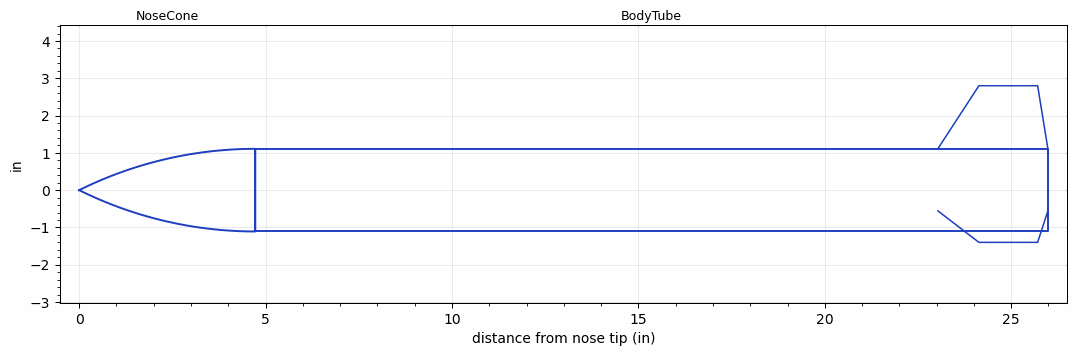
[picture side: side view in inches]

<RASAeroDocument>
 <FileVersion>2</FileVersion>
 <RocketDesign>
  <NoseCone>
   <Length>4.7244</Length>
   <Diameter>2.2165</Diameter>
   <Shape>Tangent Ogive</Shape>
   <Location>0</Location>
  </NoseCone>
  <BodyTube>
   <Length>21.2598</Length>
   <Diameter>2.2165</Diameter>
   <LaunchLugDiameter>0.3937</LaunchLugDiameter>
   <LaunchLugLength>1.1811</LaunchLugLength>
   <Location>4.7244</Location>
   <Fin>
    <Count>3</Count>
    <Chord>2.9527</Chord>
    <Span>1.6929</Span>
    <SweepDistance>1.1024</SweepDistance>
    <TipChord>1.5748</TipChord>
    <Thickness>0.1575</Thickness>
    <Location>2.9527</Location>
    <AirfoilSection>Rounded</AirfoilSection>
   </Fin>
  </BodyTube>
  <Surface>Rough Camouflage Paint</Surface>
  <ModifiedBarrowman>False</ModifiedBarrowman>
  <Turbulence>False</Turbulence>
  <UseBooster1>False</UseBooster1>
  <UseBooster2>False</UseBooster2>
 </RocketDesign>
 <LaunchSite>
  <Altitude>0</Altitude>
  <Pressure>29.9214</Pressure>
  <RodAngle>0</RodAngle>
  <RodLength>78.74</RodLength>
  <Temperature>59</Temperature>
  <WindSpeed>4.4739</WindSpeed>
 </LaunchSite>
 <Recovery>
  <Altitude1>656.168</Altitude1>
  <Altitude2>0</Altitude2>
  <DeviceType1>Parachute</DeviceType1>
  <DeviceType2>None</DeviceType2>
  <Event1>True</Event1>
  <Event2>False</Event2>
  <Size1>11.811</Size1>
  <Size2>0</Size2>
  <EventType1>Apogee</EventType1>
  <EventType2>None</EventType2>
  <CD1>0.8</CD1>
  <CD2>0</CD2>
 </Recovery>
 <SimulationList>
  <Simulation>
   <SustainerEngine>F12J  (AT)</SustainerEngine>
   <SustainerLaunchWt>1.23</SustainerLaunchWt>
   <SustainerCG>13.58</SustainerCG>
   <SustainerIgnitionDelay>0</SustainerIgnitionDelay>
   <Booster1SeparationDelay>0</Booster1SeparationDelay>
   <Booster1IgnitionDelay>0</Booster1IgnitionDelay>
   <IncludeBooster1>False</IncludeBooster1>
   <Booster2Delay>0</Booster2Delay>
   <IncludeBooster2>False</IncludeBooster2>
  </Simulation>
  <Simulation>
   <SustainerEngine>F12J  (AT)</SustainerEngine>
   <SustainerLaunchWt>1.28</SustainerLaunchWt>
   <SustainerCG>14.04</SustainerCG>
   <SustainerIgnitionDelay>0</SustainerIgnitionDelay>
   <Booster1SeparationDelay>0</Booster1SeparationDelay>
   <Booster1IgnitionDelay>0</Booster1IgnitionDelay>
   <IncludeBooster1>False</IncludeBooster1>
   <Booster2Delay>0</Booster2Delay>
   <IncludeBooster2>False</IncludeBooster2>
  </Simulation>
  <Simulation>
   <SustainerLaunchWt>1.2697</SustainerLaunchWt>
   <SustainerCG>13.8432</SustainerCG>
   <SustainerIgnitionDelay>0</SustainerIgnitionDelay>
   <Booster1SeparationDelay>0</Booster1SeparationDelay>
   <Booster1IgnitionDelay>0</Booster1IgnitionDelay>
   <IncludeBooster1>False</IncludeBooster1>
   <Booster2Delay>0</Booster2Delay>
   <IncludeBooster2>False</IncludeBooster2>
  </Simulation>
  <Simulation>
   <SustainerEngine>E30T  (AT)</SustainerEngine>
   <SustainerLaunchWt>1.2395</SustainerLaunchWt>
   <SustainerCG>13.6696</SustainerCG>
   <SustainerIgnitionDelay>0</SustainerIgnitionDelay>
   <Booster1SeparationDelay>0</Booster1SeparationDelay>
   <Booster1IgnitionDelay>0</Booster1IgnitionDelay>
   <IncludeBooster1>False</IncludeBooster1>
   <Booster2Delay>0</Booster2Delay>
   <IncludeBooster2>False</IncludeBooster2>
  </Simulation>
  <Simulation>
   <SustainerEngine>F44W  (AT)</SustainerEngine>
   <SustainerLaunchWt>1.2417</SustainerLaunchWt>
   <SustainerCG>13.689</SustainerCG>
   <SustainerIgnitionDelay>0</SustainerIgnitionDelay>
   <Booster1SeparationDelay>0</Booster1SeparationDelay>
   <Booster1IgnitionDelay>0</Booster1IgnitionDelay>
   <IncludeBooster1>False</IncludeBooster1>
   <Booster2Delay>0</Booster2Delay>
   <IncludeBooster2>False</IncludeBooster2>
  </Simulation>
  <Simulation>
   <SustainerEngine>F44W  (AT)</SustainerEngine>
   <SustainerLaunchWt>1.2417</SustainerLaunchWt>
   <SustainerCG>13.689</SustainerCG>
   <SustainerIgnitionDelay>0</SustainerIgnitionDelay>
   <Booster1SeparationDelay>0</Booster1SeparationDelay>
   <Booster1IgnitionDelay>0</Booster1IgnitionDelay>
   <IncludeBooster1>False</IncludeBooster1>
   <Booster2Delay>0</Booster2Delay>
   <IncludeBooster2>False</IncludeBooster2>
  </Simulation>
 </SimulationList>
</RASAeroDocument>
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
